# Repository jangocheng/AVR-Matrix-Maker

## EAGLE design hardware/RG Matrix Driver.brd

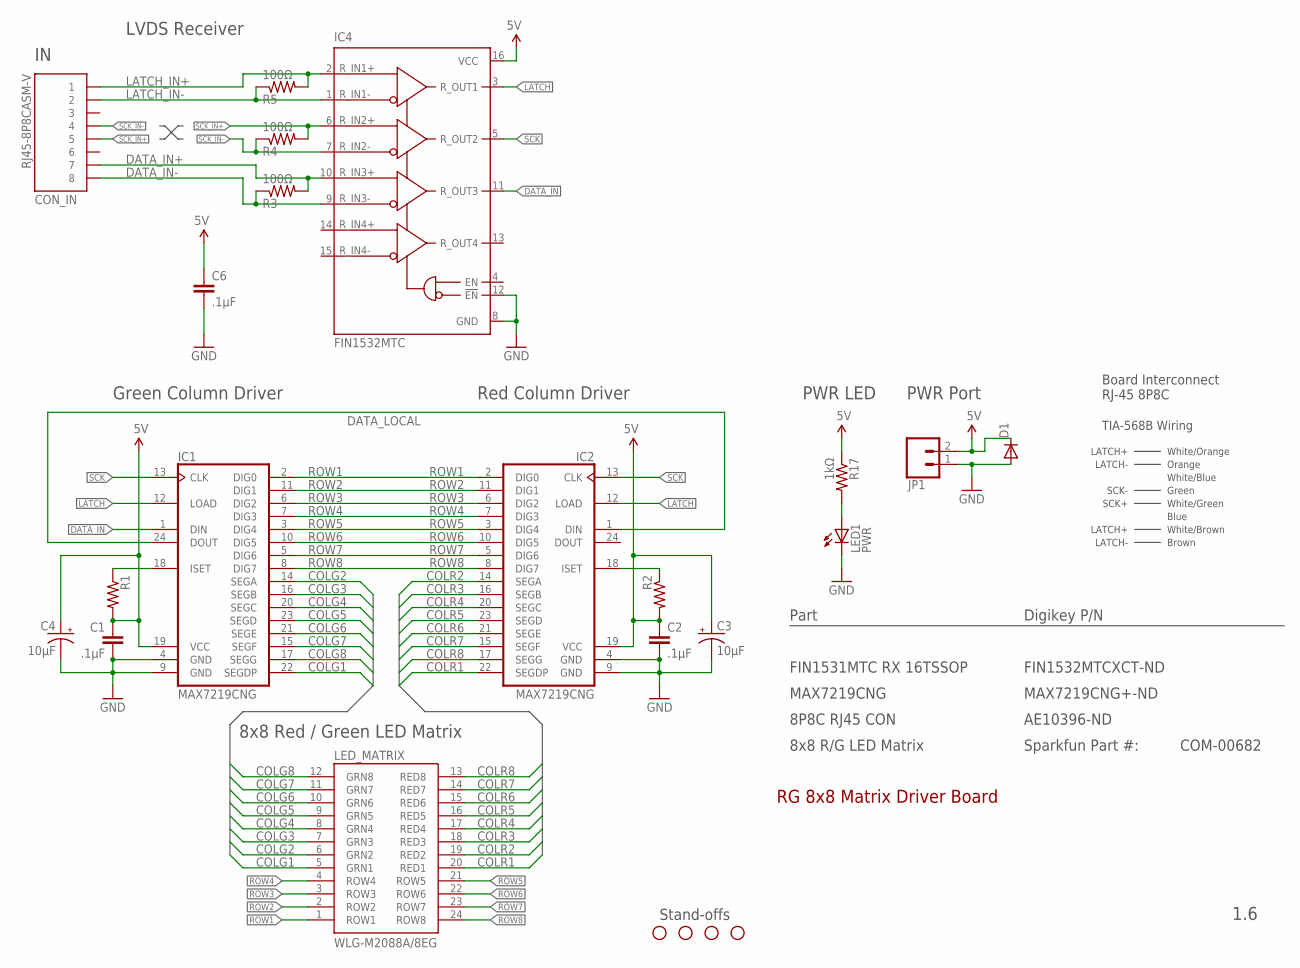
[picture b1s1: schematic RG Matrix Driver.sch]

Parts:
C1, C2, C6: .1µF; 1206
C3, C4: 10µF; CPOL-RADIAL-10UF-25V
CON_IN: RJ45-8P8CASM-V; RJ45-8P8C-ASM
D1: DIODEPTH; DIODE-1N4001
IC1, IC2: MAX7219CNG; DIL24-3
IC4: FIN1532MTC; TSSOP-16
JP1: PWR; 1X02_PC_SMD
JP3, JP4, JP5, JP6: STAND-OFF
LED1: PWR; LED-1206
LED_MATRIX: WLG-M2088A/8EG
R1, R2: RESISTOR1206; 1206
R3, R4, R5: 100Ω; 1206
R17: 1kΩ; 1206

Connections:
5V: C1.1, C2.1, C3.1 (+), C4.1 (+), C6.1, D1.C, IC1.19 (VCC), IC2.19 (VCC), IC4.16 (VCC), JP1.2, R1.2, R2.2, R17.1
COLG1: IC1.22 (SEGDP), LED_MATRIX.5 (GRN1)
COLG2: IC1.14 (SEGA), LED_MATRIX.6 (GRN2)
COLG3: IC1.16 (SEGB), LED_MATRIX.7 (GRN3)
COLG4: IC1.20 (SEGC), LED_MATRIX.8 (GRN4)
COLG5: IC1.23 (SEGD), LED_MATRIX.9 (GRN5)
COLG6: IC1.21 (SEGE), LED_MATRIX.10 (GRN6)
COLG7: IC1.15 (SEGF), LED_MATRIX.11 (GRN7)
COLG8: IC1.17 (SEGG), LED_MATRIX.12 (GRN8)
COLR1: IC2.22 (SEGDP), LED_MATRIX.20 (RED1)
COLR2: IC2.14 (SEGA), LED_MATRIX.19 (RED2)
COLR3: IC2.16 (SEGB), LED_MATRIX.18 (RED3)
COLR4: IC2.20 (SEGC), LED_MATRIX.17 (RED4)
COLR5: IC2.23 (SEGD), LED_MATRIX.16 (RED5)
COLR6: IC2.21 (SEGE), LED_MATRIX.15 (RED6)
COLR7: IC2.15 (SEGF), LED_MATRIX.14 (RED7)
COLR8: IC2.17 (SEGG), LED_MATRIX.13 (RED8)
DATA_IN: IC1.1 (DIN), IC4.11 (R_OUT3)
DATA_IN+: CON_IN.7, IC4.10 (R_IN3+), R3.2
DATA_IN-: CON_IN.8, IC4.9 (R_IN3-), R3.1
DATA_LOCAL: IC1.24 (DOUT), IC2.1 (DIN)
GISET: IC1.18 (ISET), R1.1
GND: C1.2, C2.2, C3.2 (-), C4.2 (-), C6.2, D1.A, IC1.4 (GND), IC1.9 (GND), IC2.4 (GND), IC2.9 (GND), IC4.8 (GND), IC4.12 (!EN), JP1.1, LED1.C
LATCH: IC1.12 (LOAD), IC2.12 (LOAD), IC4.3 (R_OUT1)
LATCH_IN+: CON_IN.1, IC4.2 (R_IN1+), R5.2
LATCH_IN-: CON_IN.2, IC4.1 (R_IN1-), R5.1
LEDPWR: LED1.A, R17.2
RISET: IC2.18 (ISET), R2.1
ROW1: IC1.2 (DIG0), IC2.2 (DIG0), LED_MATRIX.1 (ROW1)
ROW2: IC1.11 (DIG1), IC2.11 (DIG1), LED_MATRIX.2 (ROW2)
ROW3: IC1.6 (DIG2), IC2.6 (DIG2), LED_MATRIX.3 (ROW3)
ROW4: IC1.7 (DIG3), IC2.7 (DIG3), LED_MATRIX.4 (ROW4)
ROW5: IC1.3 (DIG4), IC2.3 (DIG4), LED_MATRIX.21 (ROW5)
ROW6: IC1.10 (DIG5), IC2.10 (DIG5), LED_MATRIX.22 (ROW6)
ROW7: IC1.5 (DIG6), IC2.5 (DIG6), LED_MATRIX.23 (ROW7)
ROW8: IC1.8 (DIG7), IC2.8 (DIG7), LED_MATRIX.24 (ROW8)
SCK: IC1.13 (CLK), IC2.13 (CLK), IC4.5 (R_OUT2)
SCK_IN+: CON_IN.5, IC4.6 (R_IN2+), R4.2
SCK_IN-: CON_IN.4, IC4.7 (R_IN2-), R4.1

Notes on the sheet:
Green Column Driver
Red Column Driver
8x8 Red / Green LED Matrix
PWR Port
PWR LED
Board Interconnect RJ-45 8P8C
RG 8x8 Matrix Driver Board
LVDS Receiver
White/Orange
Orange
White/Blue
Green
White/Green
Blue
White/Brown
Brown
TIA-568B Wiring
1.6
LATCH+
LATCH-
SCK-
SCK+
Part
Digikey P/N
FIN1531MTC RX 16TSSOP
FIN1532MTCXCT-ND
MAX7219CNG
MAX7219CNG+-ND
8P8C RJ45 CON
AE10396-ND
8x8 R/G LED Matrix
Sparkfun Part #:
COM-00682
Stand-offs

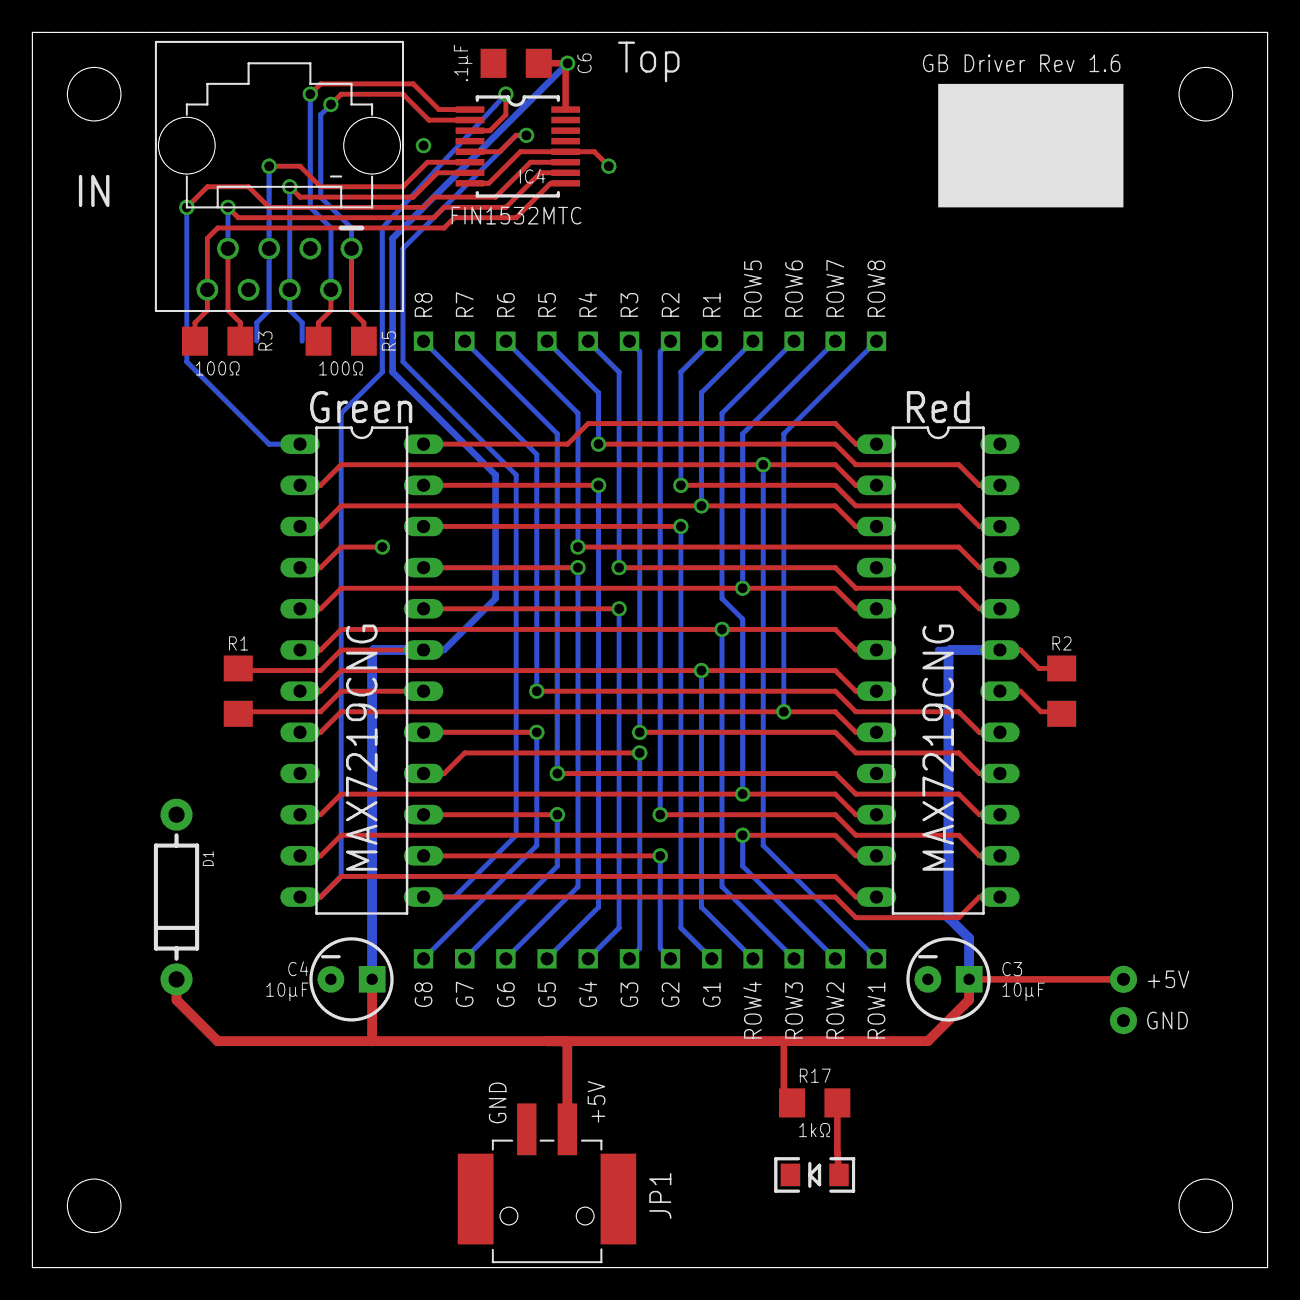
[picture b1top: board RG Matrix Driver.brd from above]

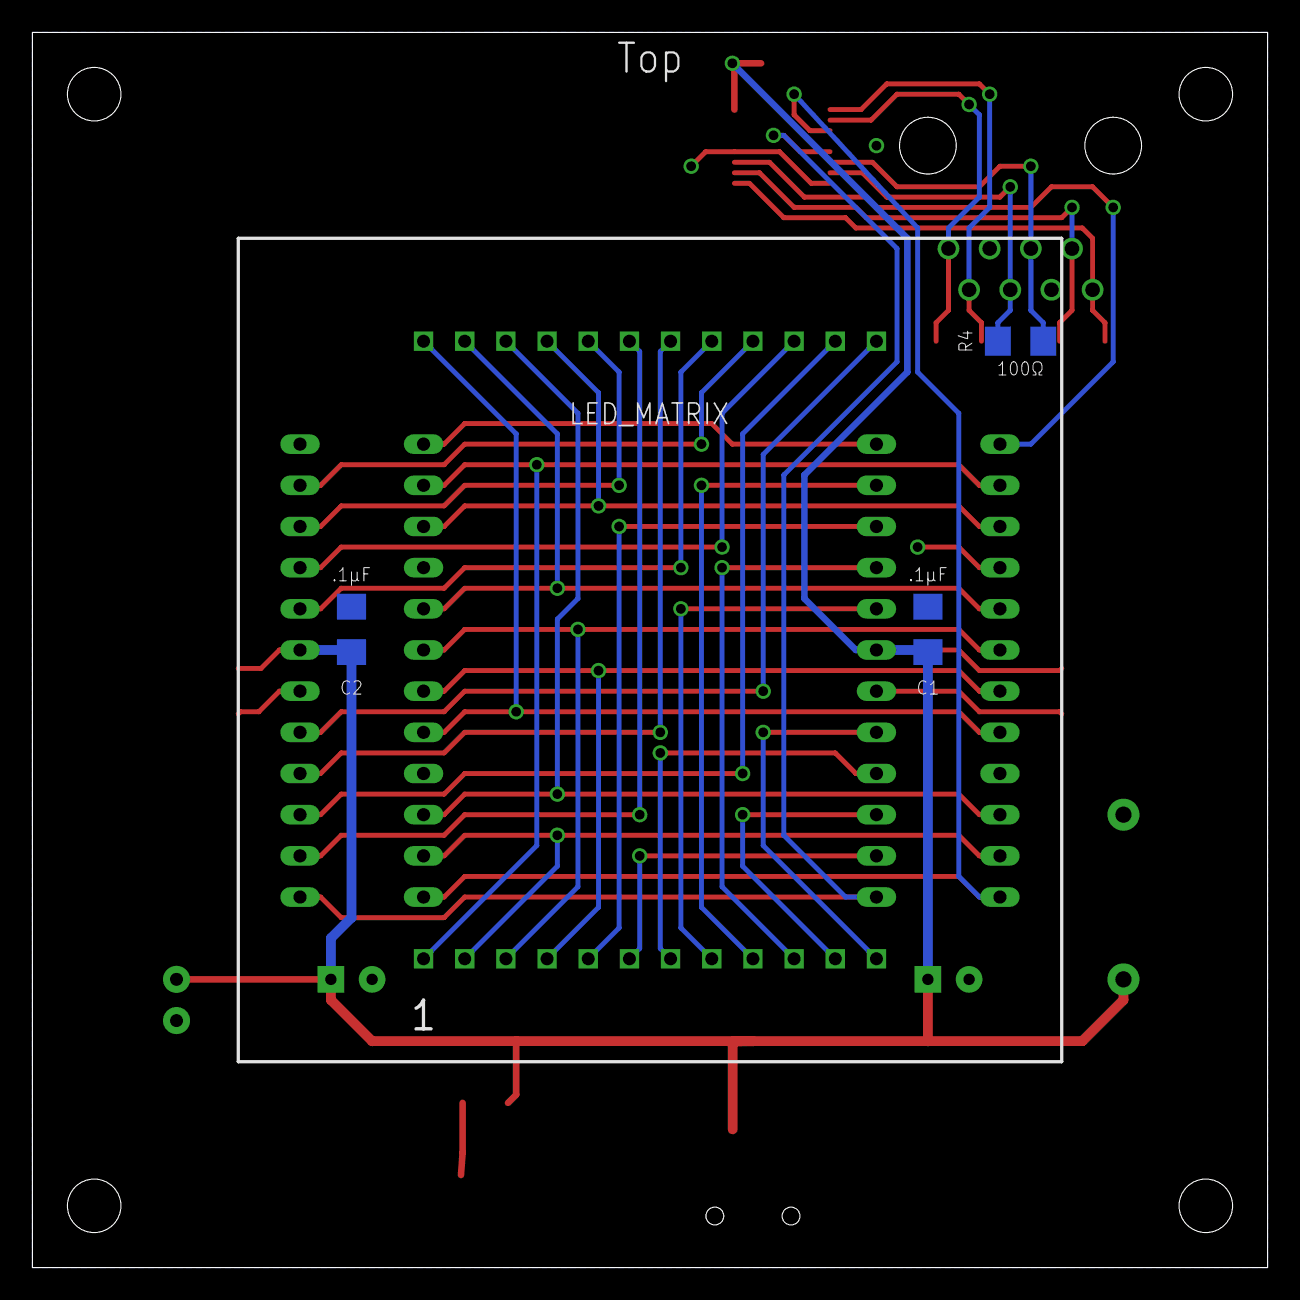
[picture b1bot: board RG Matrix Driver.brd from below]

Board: 2 copper layers, 76.2 x 76.2 mm, 23 parts (4 on the bottom side), 39 nets.

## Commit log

2016-04-20 Added Eagle files
2016-04-20 Added PDFs
2016-04-20 Moved hardware to separate repository
2016-07-07 New makefile, updated project build settings
2016-07-07 updated gitignore_

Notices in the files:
parts and their libraries:
SparkFun: Licensing: CC v3.0 Share-Alike You are welcome to use this library for commercial purposes.
SparkFun-Capacitors: Licensing: Creative Commons ShareAlike 4.0 International - https://creativecommons.org/licenses/by-sa/4.0
